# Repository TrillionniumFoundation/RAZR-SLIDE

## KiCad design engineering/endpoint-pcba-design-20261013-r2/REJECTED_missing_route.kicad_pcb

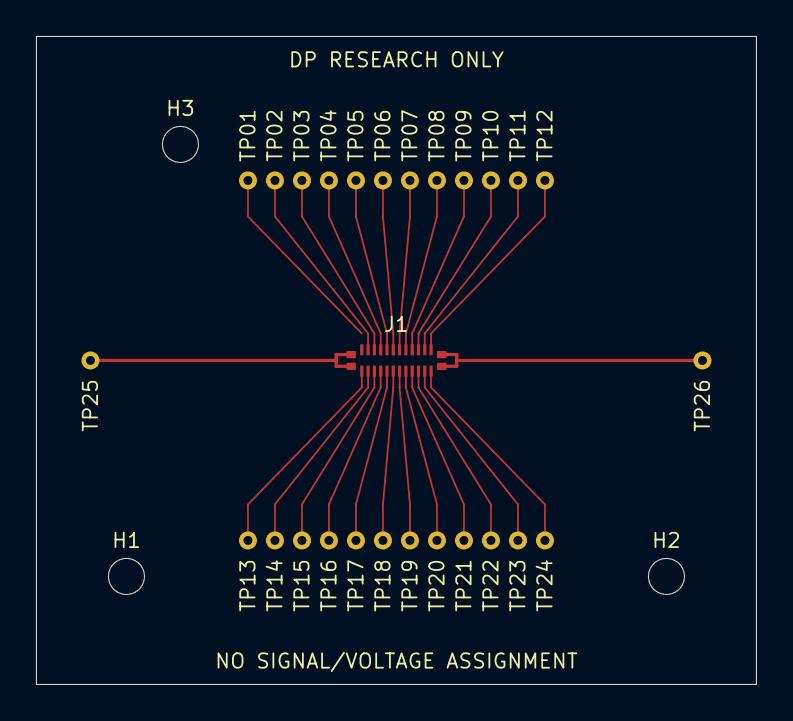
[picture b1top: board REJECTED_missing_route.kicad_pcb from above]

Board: 2 copper layers, 40.0 x 36.0 mm, 30 parts (0 on the bottom side), 26 nets.

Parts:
H1, H2, H3: FIXTURE_DATUM_UNQUALIFIED; Datum_2mm_NPTH
J1: BM28_24DP_RESEARCH; Hirose_BM28B0.6-24DP_2-0.35V_53_RESEARCH_PHYSICAL_SITES
TP01: PROBE_ONLY_S_NEG_00; ProbePad_1mm_NO_PASTE
TP02: PROBE_ONLY_S_NEG_01; ProbePad_1mm_NO_PASTE
TP03: PROBE_ONLY_S_NEG_02; ProbePad_1mm_NO_PASTE
TP04: PROBE_ONLY_S_NEG_03; ProbePad_1mm_NO_PASTE
TP05: PROBE_ONLY_S_NEG_04; ProbePad_1mm_NO_PASTE
TP06: PROBE_ONLY_S_NEG_05; ProbePad_1mm_NO_PASTE
TP07: PROBE_ONLY_S_NEG_06; ProbePad_1mm_NO_PASTE
TP08: PROBE_ONLY_S_NEG_07; ProbePad_1mm_NO_PASTE
TP09: PROBE_ONLY_S_NEG_08; ProbePad_1mm_NO_PASTE
TP10: PROBE_ONLY_S_NEG_09; ProbePad_1mm_NO_PASTE
TP11: PROBE_ONLY_S_NEG_10; ProbePad_1mm_NO_PASTE
TP12: PROBE_ONLY_S_NEG_11; ProbePad_1mm_NO_PASTE
TP13: PROBE_ONLY_S_POS_00; ProbePad_1mm_NO_PASTE
TP14: PROBE_ONLY_S_POS_01; ProbePad_1mm_NO_PASTE
TP15: PROBE_ONLY_S_POS_02; ProbePad_1mm_NO_PASTE
TP16: PROBE_ONLY_S_POS_03; ProbePad_1mm_NO_PASTE
TP17: PROBE_ONLY_S_POS_04; ProbePad_1mm_NO_PASTE
TP18: PROBE_ONLY_S_POS_05; ProbePad_1mm_NO_PASTE
TP19: PROBE_ONLY_S_POS_06; ProbePad_1mm_NO_PASTE
TP20: PROBE_ONLY_S_POS_07; ProbePad_1mm_NO_PASTE
TP21: PROBE_ONLY_S_POS_08; ProbePad_1mm_NO_PASTE
TP22: PROBE_ONLY_S_POS_09; ProbePad_1mm_NO_PASTE
TP23: PROBE_ONLY_S_POS_10; ProbePad_1mm_NO_PASTE
TP24: PROBE_ONLY_S_POS_11; ProbePad_1mm_NO_PASTE
TP25: PROBE_ONLY_P_L; ProbePad_1mm_NO_PASTE
TP26: PROBE_ONLY_P_R; ProbePad_1mm_NO_PASTE

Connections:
C01: J1.S_NEG_00, TP01.1
C02: J1.S_NEG_01, TP02.1
C03: J1.S_NEG_02, TP03.1
C04: J1.S_NEG_03, TP04.1
C05: J1.S_NEG_04, TP05.1
C06: J1.S_NEG_05, TP06.1
C07: J1.S_NEG_06, TP07.1
C08: J1.S_NEG_07, TP08.1
C09: J1.S_NEG_08, TP09.1
C10: J1.S_NEG_09, TP10.1
C11: J1.S_NEG_10, TP11.1
C12: J1.S_NEG_11, TP12.1
C13: J1.S_POS_00, TP13.1
C14: J1.S_POS_01, TP14.1
C15: J1.S_POS_02, TP15.1
C16: J1.S_POS_03, TP16.1
C17: J1.S_POS_04, TP17.1
C18: J1.S_POS_05, TP18.1
C19: J1.S_POS_06, TP19.1
C20: J1.S_POS_07, TP20.1
C21: J1.S_POS_08, TP21.1
C22: J1.S_POS_09, TP22.1
C23: J1.S_POS_10, TP23.1
C24: J1.S_POS_11, TP24.1
C25: J1.P_L, TP25.1
C26: J1.P_R, TP26.1

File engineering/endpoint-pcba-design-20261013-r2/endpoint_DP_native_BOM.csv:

reference,value,footprint,procurement_role
J1,BM28_24DP_COORDINATE_SITES,RAZR_ENDPOINT_RESEARCH:Hirose_BM28B0.6-24DP_2-0.35V_53_RESEARCH_PHYSICAL_SITES,connector only
TP01,PROBE_S_NEG_00,Owned_Coupon:ProbePad_1mm_NO_PASTE,PCB probe feature; no discrete part
TP02,PROBE_S_NEG_01,Owned_Coupon:ProbePad_1mm_NO_PASTE,PCB probe feature; no discrete part
TP03,PROBE_S_NEG_02,Owned_Coupon:ProbePad_1mm_NO_PASTE,PCB probe feature; no discrete part
TP04,PROBE_S_NEG_03,Owned_Coupon:ProbePad_1mm_NO_PASTE,PCB probe feature; no discrete part
TP05,PROBE_S_NEG_04,Owned_Coupon:ProbePad_1mm_NO_PASTE,PCB probe feature; no discrete part
TP06,PROBE_S_NEG_05,Owned_Coupon:ProbePad_1mm_NO_PASTE,PCB probe feature; no discrete part
TP07,PROBE_S_NEG_06,Owned_Coupon:ProbePad_1mm_NO_PASTE,PCB probe feature; no discrete part
TP08,PROBE_S_NEG_07,Owned_Coupon:ProbePad_1mm_NO_PASTE,PCB probe feature; no discrete part
TP09,PROBE_S_NEG_08,Owned_Coupon:ProbePad_1mm_NO_PASTE,PCB probe feature; no discrete part
TP10,PROBE_S_NEG_09,Owned_Coupon:ProbePad_1mm_NO_PASTE,PCB probe feature; no discrete part
TP11,PROBE_S_NEG_10,Owned_Coupon:ProbePad_1mm_NO_PASTE,PCB probe feature; no discrete part
TP12,PROBE_S_NEG_11,Owned_Coupon:ProbePad_1mm_NO_PASTE,PCB probe feature; no discrete part
TP13,PROBE_S_POS_00,Owned_Coupon:ProbePad_1mm_NO_PASTE,PCB probe feature; no discrete part
TP14,PROBE_S_POS_01,Owned_Coupon:ProbePad_1mm_NO_PASTE,PCB probe feature; no discrete part
TP15,PROBE_S_POS_02,Owned_Coupon:ProbePad_1mm_NO_PASTE,PCB probe feature; no discrete part
TP16,PROBE_S_POS_03,Owned_Coupon:ProbePad_1mm_NO_PASTE,PCB probe feature; no discrete part
TP17,PROBE_S_POS_04,Owned_Coupon:ProbePad_1mm_NO_PASTE,PCB probe feature; no discrete part
TP18,PROBE_S_POS_05,Owned_Coupon:ProbePad_1mm_NO_PASTE,PCB probe feature; no discrete part
TP19,PROBE_S_POS_06,Owned_Coupon:ProbePad_1mm_NO_PASTE,PCB probe feature; no discrete part
TP20,PROBE_S_POS_07,Owned_Coupon:ProbePad_1mm_NO_PASTE,PCB probe feature; no discrete part
TP21,PROBE_S_POS_08,Owned_Coupon:ProbePad_1mm_NO_PASTE,PCB probe feature; no discrete part
TP22,PROBE_S_POS_09,Owned_Coupon:ProbePad_1mm_NO_PASTE,PCB probe feature; no discrete part
TP23,PROBE_S_POS_10,Owned_Coupon:ProbePad_1mm_NO_PASTE,PCB probe feature; no discrete part
TP24,PROBE_S_POS_11,Owned_Coupon:ProbePad_1mm_NO_PASTE,PCB probe feature; no discrete part
TP25,PROBE_P_L,Owned_Coupon:ProbePad_1mm_NO_PASTE,PCB probe feature; no discrete part
TP26,PROBE_P_R,Owned_Coupon:ProbePad_1mm_NO_PASTE,PCB probe feature; no discrete part

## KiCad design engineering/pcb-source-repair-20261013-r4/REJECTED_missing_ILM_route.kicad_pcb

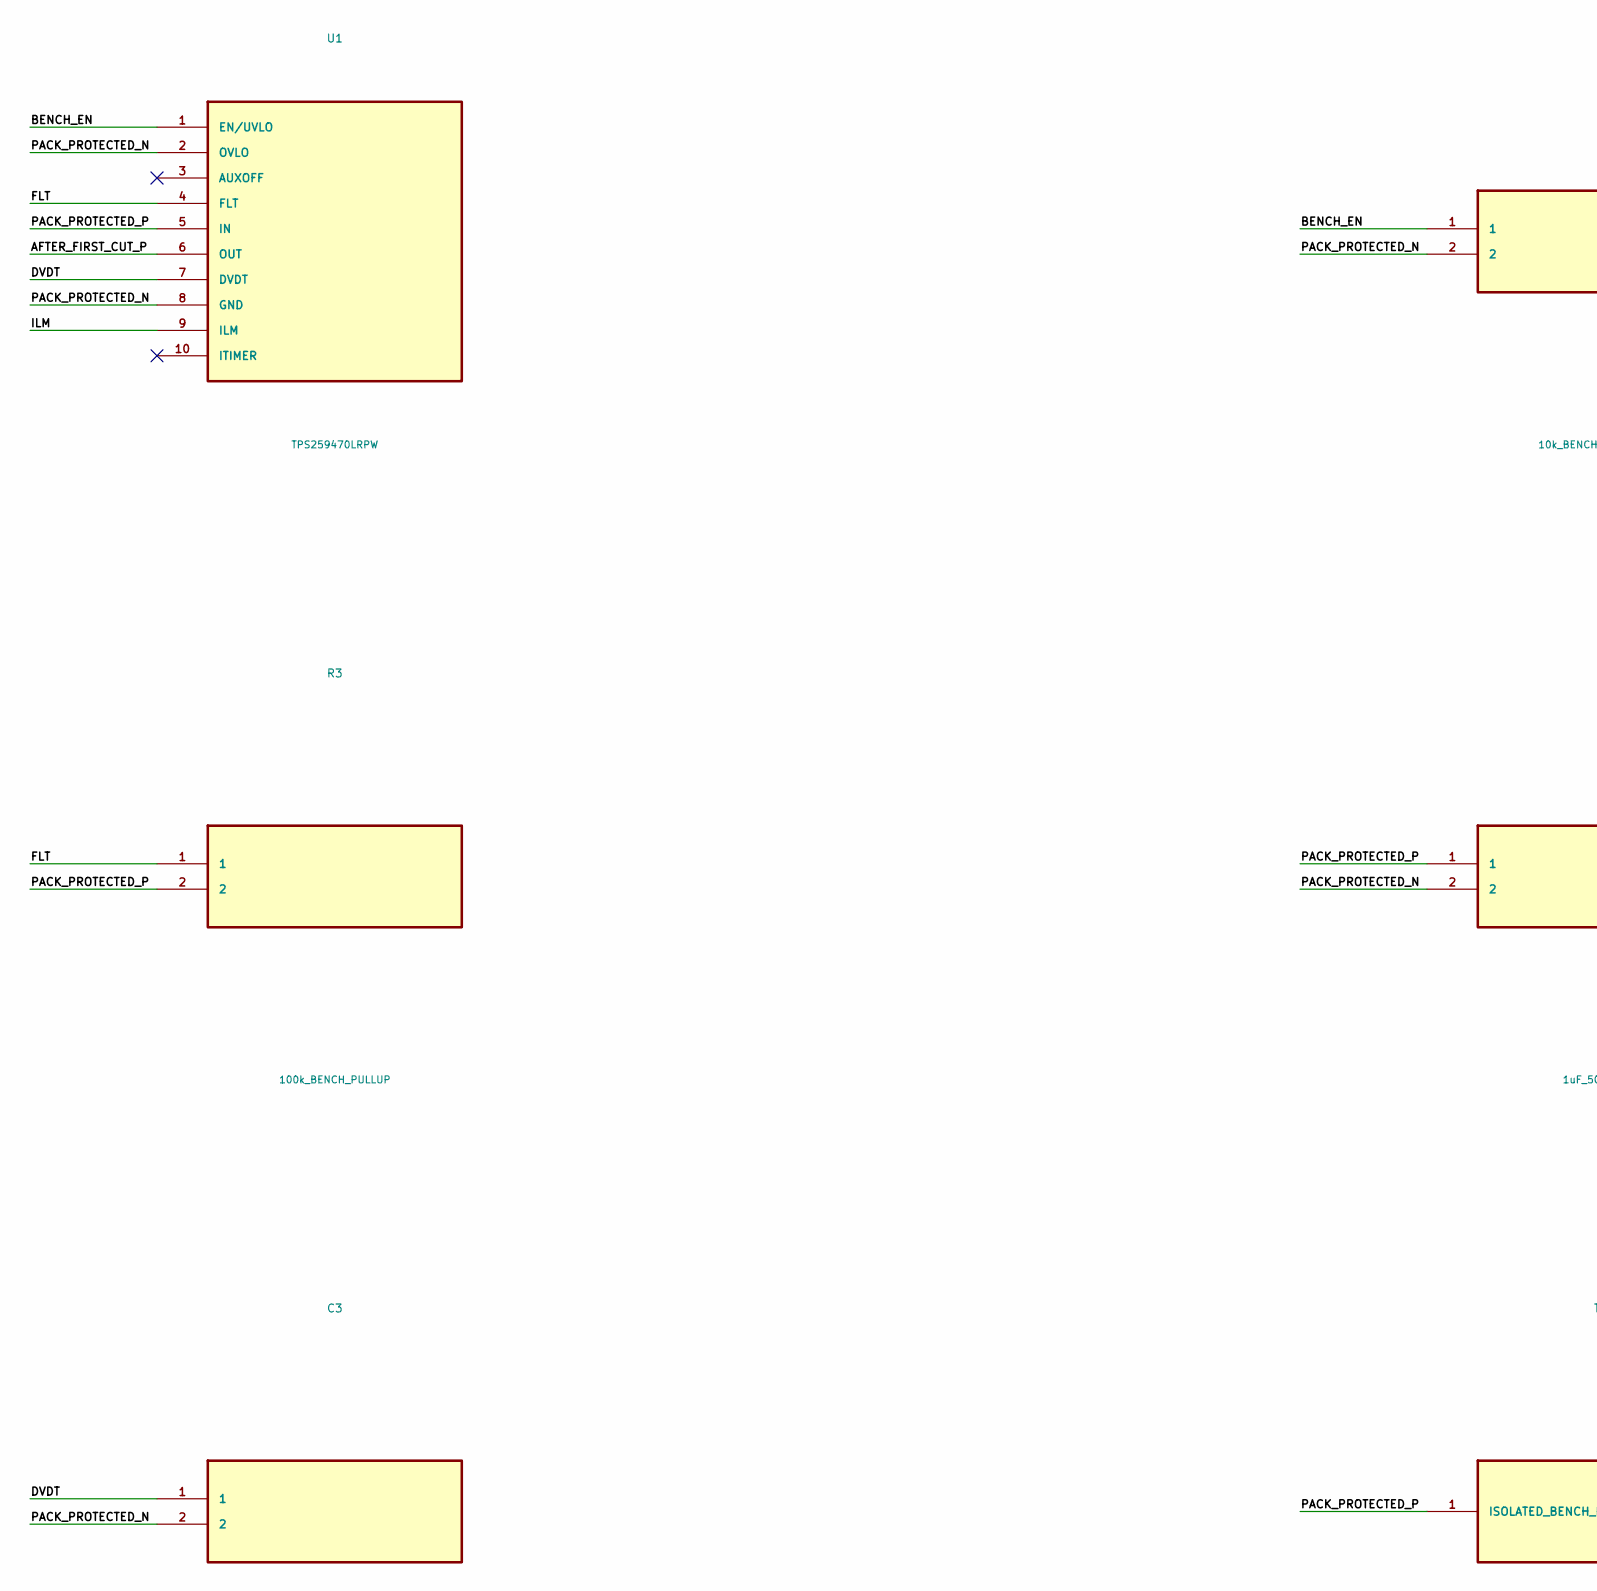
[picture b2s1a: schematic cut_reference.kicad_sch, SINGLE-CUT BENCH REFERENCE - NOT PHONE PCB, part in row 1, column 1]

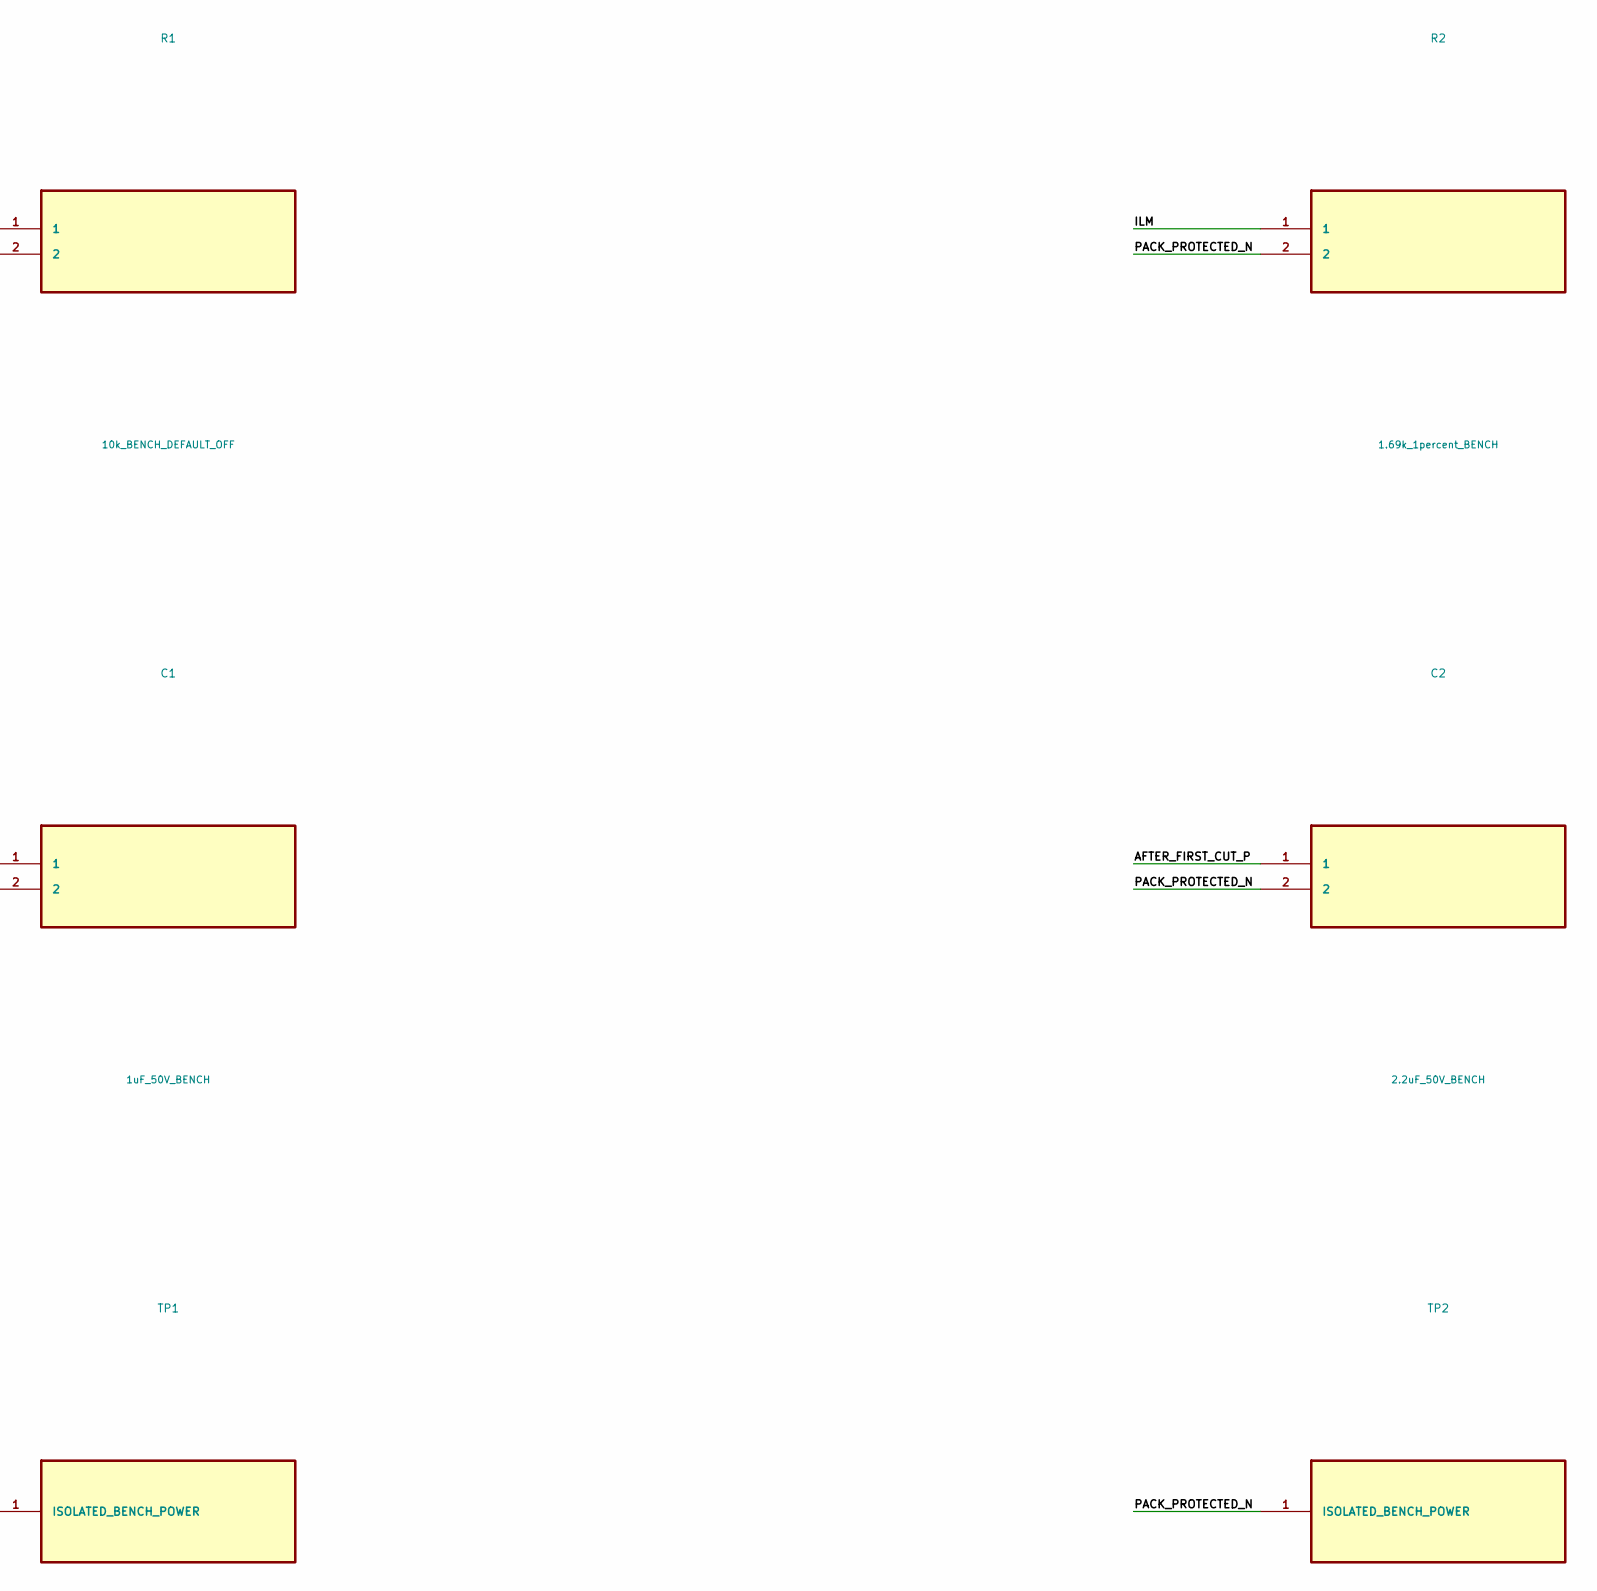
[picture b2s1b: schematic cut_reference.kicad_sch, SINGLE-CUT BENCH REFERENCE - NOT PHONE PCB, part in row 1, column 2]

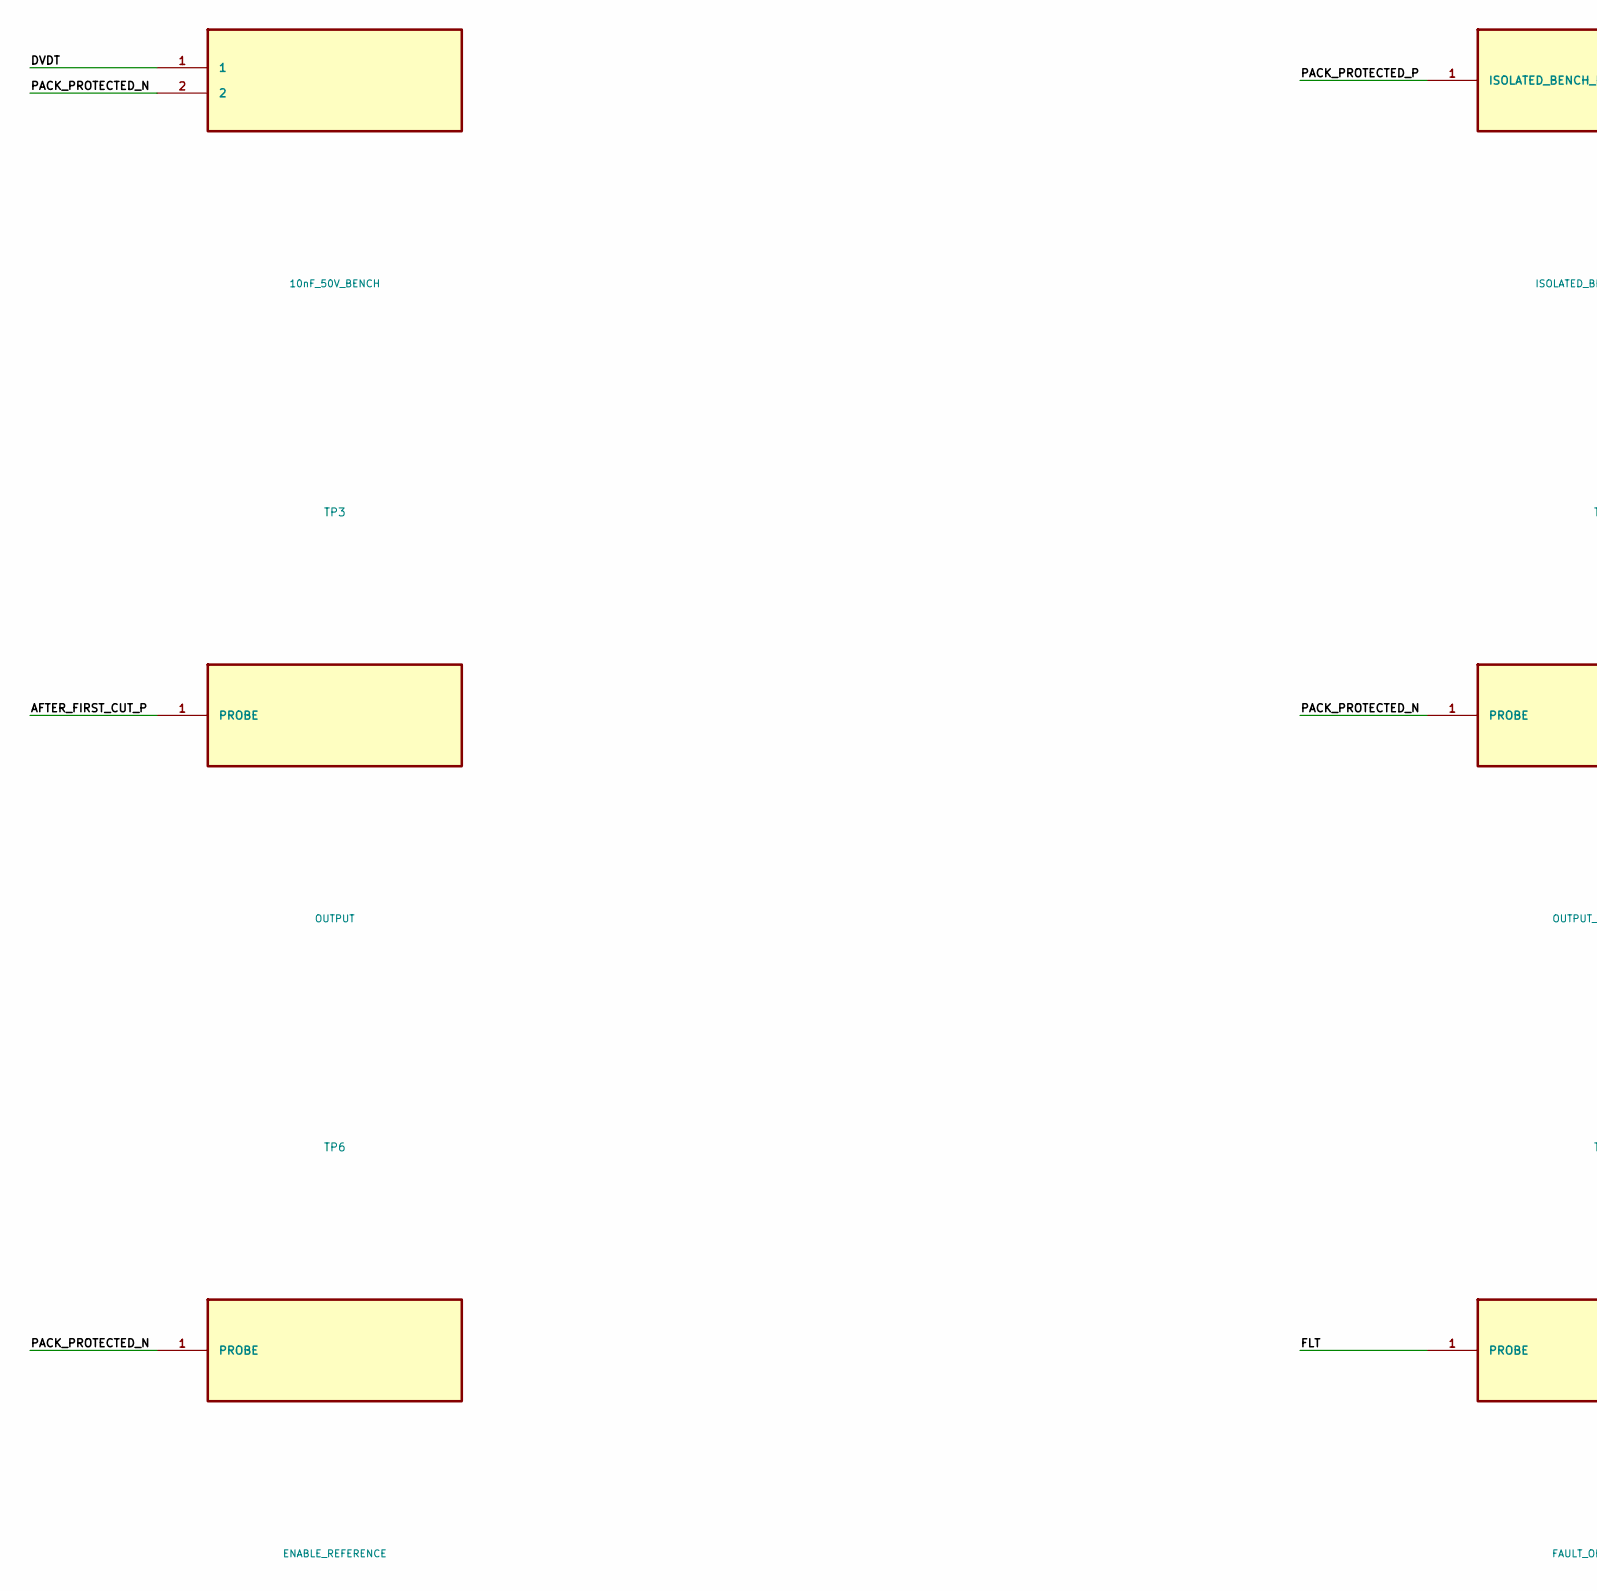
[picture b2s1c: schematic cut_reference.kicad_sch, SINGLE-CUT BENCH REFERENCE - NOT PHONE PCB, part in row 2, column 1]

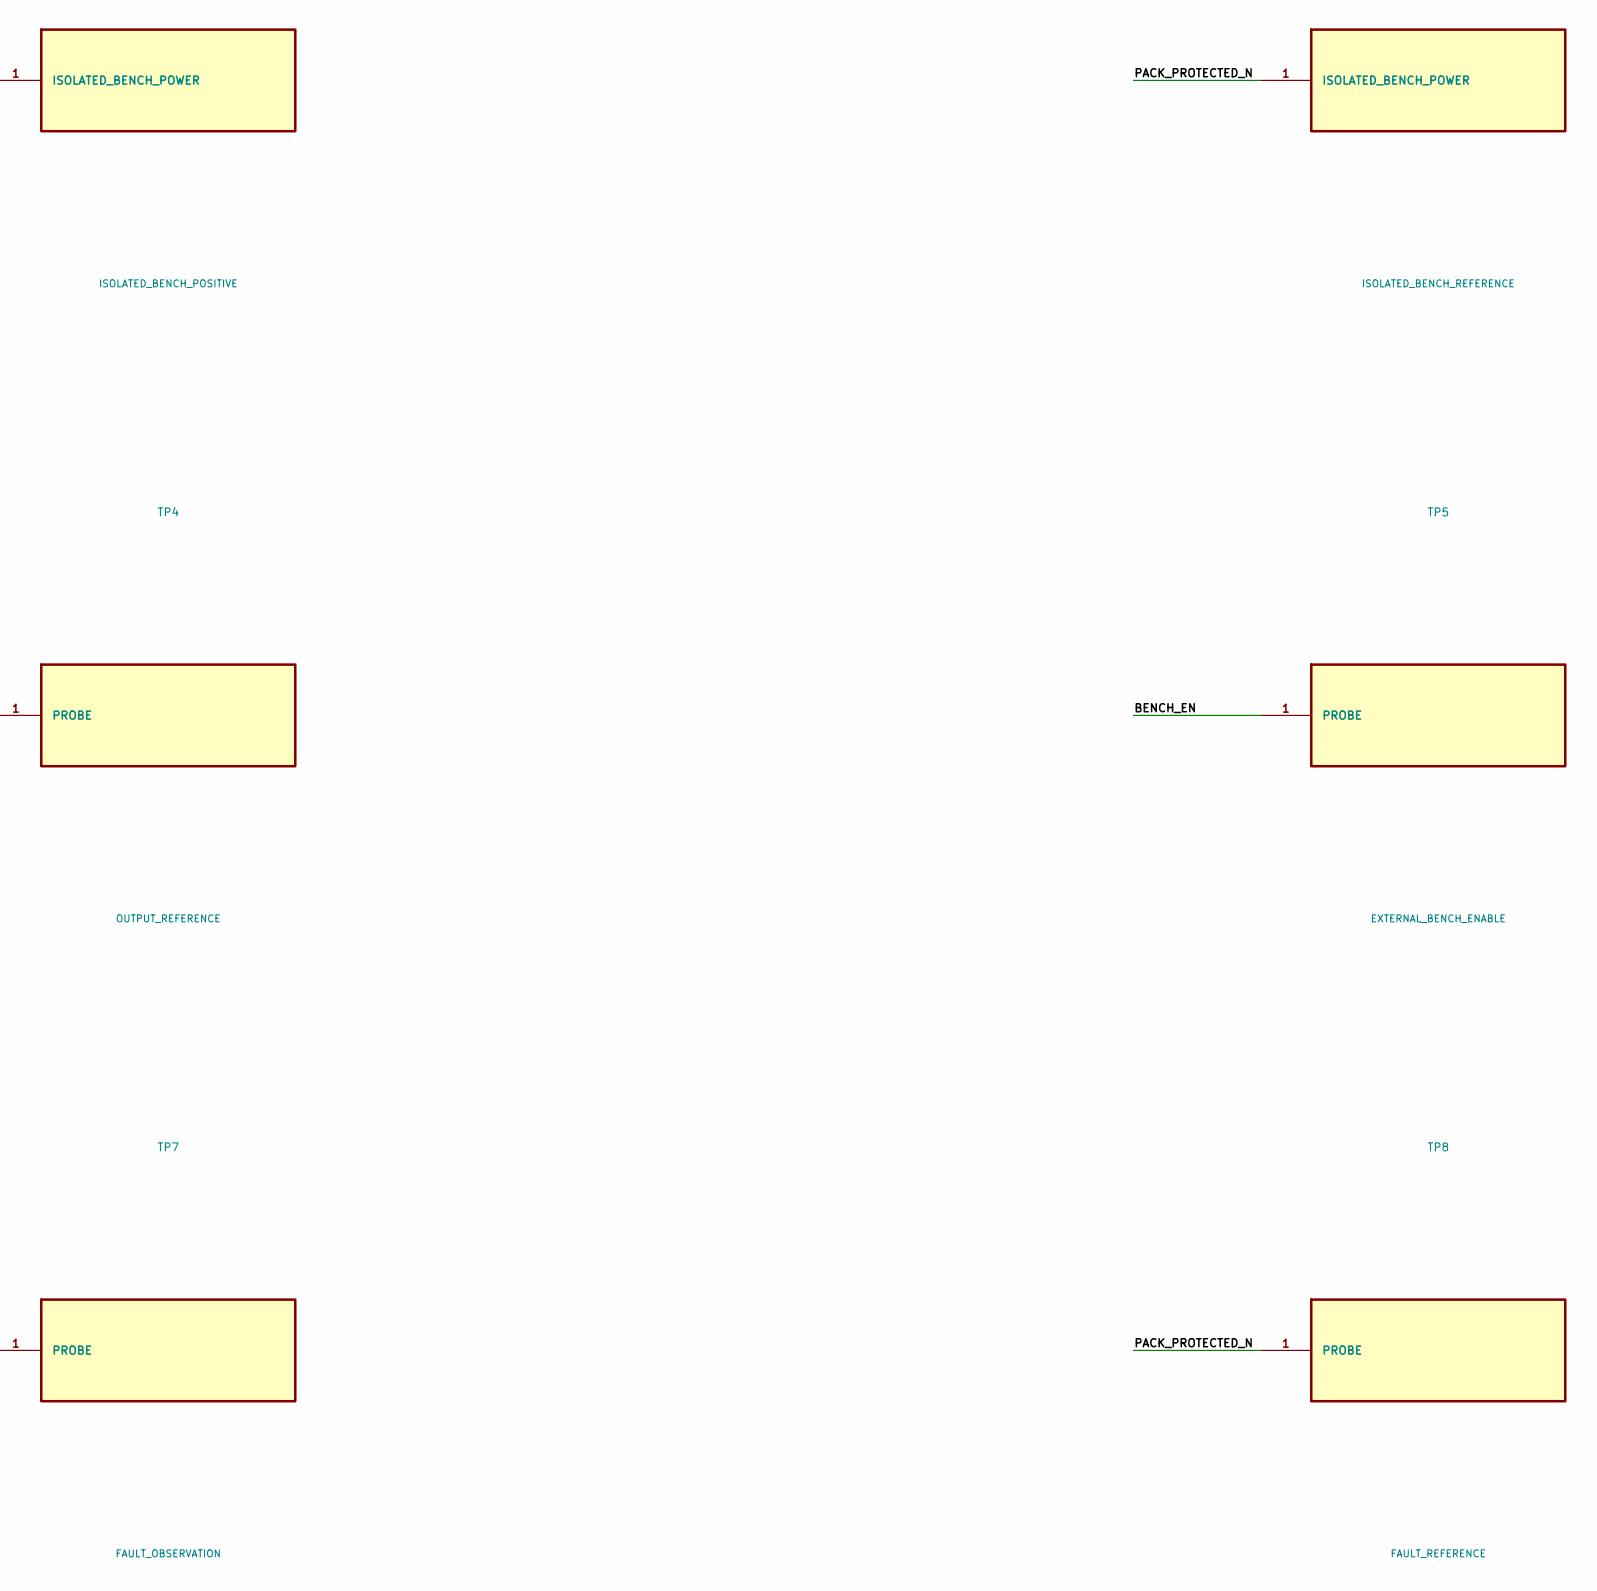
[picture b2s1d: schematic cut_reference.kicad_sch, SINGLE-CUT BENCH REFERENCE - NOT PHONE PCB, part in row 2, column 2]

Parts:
C1: 1uF_50V_BENCH; Passive_0805_BENCH
C2: 2.2uF_50V_BENCH; Passive_0805_BENCH
C3: 10nF_50V_BENCH; Passive_0805_BENCH
R1: 10k_BENCH_DEFAULT_OFF; Passive_0805_Vertical_BENCH
R2: 1.69k_1percent_BENCH; Passive_0805_BENCH
R3: 100k_BENCH_PULLUP; Passive_0805_BENCH
TP1: ISOLATED_BENCH_POSITIVE; Probe_1p8mm
TP2: ISOLATED_BENCH_REFERENCE; Probe_1p8mm
TP3: OUTPUT; Probe_1p8mm
TP4: OUTPUT_REFERENCE; Probe_1p8mm
TP5: EXTERNAL_BENCH_ENABLE; Probe_1p8mm
TP6: ENABLE_REFERENCE; Probe_1p8mm
TP7: FAULT_OBSERVATION; Probe_1p8mm
TP8: FAULT_REFERENCE; Probe_1p8mm
U1: TPS259470LRPW; RPW0010A_OWNED_NOMINAL

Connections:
AFTER_FIRST_CUT_P: C2.1, TP3.1, U1.6 (OUT)
BENCH_EN: R1.1, TP5.1, U1.1 (EN/UVLO)
DVDT: C3.1, U1.7 (DVDT)
FLT: R3.1, TP7.1, U1.4 (FLT)
ILM: R2.1, U1.9 (ILM)
PACK_PROTECTED_N: C1.2, C2.2, C3.2, R1.2, R2.2, TP2.1, TP4.1, TP6.1, TP8.1, U1.2 (OVLO), U1.8 (GND)
PACK_PROTECTED_P: C1.1, R3.2, TP1.1, U1.5 (IN)

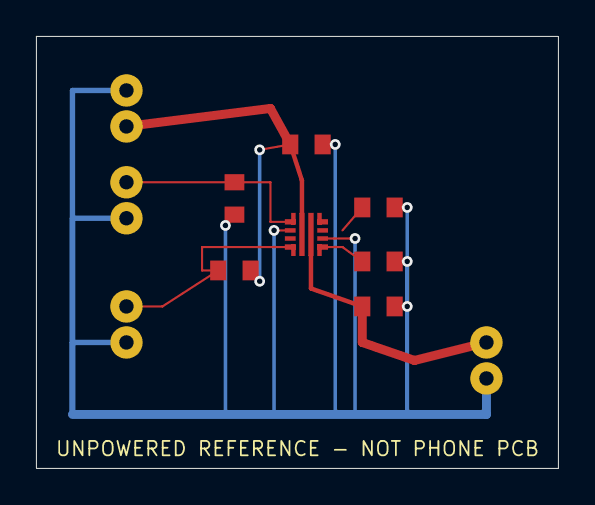
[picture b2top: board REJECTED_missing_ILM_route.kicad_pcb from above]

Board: 2 copper layers, 29.0 x 24.0 mm, 15 parts (0 on the bottom side), 7 nets.

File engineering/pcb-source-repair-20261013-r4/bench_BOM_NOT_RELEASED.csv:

ref,part,value,footprint,MPN_selected_for_phone,physical_qualified
U1,TPS259470LRPW,TPS259470LRPW,RPW0010A_OWNED_NOMINAL,False,False
R1,R,10k_BENCH_DEFAULT_OFF,Passive_0805_Vertical_BENCH,False,False
R2,R,1.69k_1percent_BENCH,Passive_0805_BENCH,False,False
R3,R,100k_BENCH_PULLUP,Passive_0805_BENCH,False,False
C1,C,1uF_50V_BENCH,Passive_0805_BENCH,False,False
C2,C,2.2uF_50V_BENCH,Passive_0805_BENCH,False,False
C3,C,10nF_50V_BENCH,Passive_0805_BENCH,False,False
TP1,BenchSource,ISOLATED_BENCH_POSITIVE,Probe_1p8mm,False,False
TP2,BenchSource,ISOLATED_BENCH_REFERENCE,Probe_1p8mm,False,False
TP3,Probe,OUTPUT,Probe_1p8mm,False,False
TP4,Probe,OUTPUT_REFERENCE,Probe_1p8mm,False,False
TP5,Probe,EXTERNAL_BENCH_ENABLE,Probe_1p8mm,False,False
TP6,Probe,ENABLE_REFERENCE,Probe_1p8mm,False,False
TP7,Probe,FAULT_OBSERVATION,Probe_1p8mm,False,False
TP8,Probe,FAULT_REFERENCE,Probe_1p8mm,False,False
